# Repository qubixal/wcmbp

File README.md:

# Water Cooled MacBookPro (WCMBP)
> _this is part of a submission to Blueprint Hack Club._

**Hello!** I'm aiming to DIY the First True* Liquid Cooled Macbook utilising a sub-2.5mm Liquid Cooling Block, as well as creating the first Active Same-Level Hybrid Air-Liquid Cooling System In Consumer Electronics.
The first part of this readme will be a short introduction before this project is explained in more depth.

_render of the stock cooler of the Macbook Pro A2442._

## Function / Use
Similar to a traditional Desktop PC AIO, it features a pump, two fans (one blower one exhaust) and a modified refrigerator heatsink for a small size. 
<br>To use this project, simply plug in the quick disconnect tubing and plug the usbc line into a Macbook that has been prefitted with the heatsink and watch temps drop. 

## Why did I start this project?
I've always wanted to start making something but never found the determination to. 
My first attempt happened last year with me challenging myself to build the smallest drone i could, though those plans were cut short by my lack of experience and shipping problems (negotiating 4 months for the pcb) that destroyed my motivation. 
I wanted to push for a pioneer and revolutionary idea that improves technology, and had an idea at the end of last year to create the world's first true liquid cooled Macbook. 

I hope to make a high quality video out of this project too!
<br> **Thank you for reviewing this project.**

note: this repository is placed under CC BY-NC-ND.

## Hardware (Cooler)
The concept is simple, just pull water over the processor ...

The first design used parallel channels running from a supply manifold to a drain manifold, shortening single channels to reduce pressure drop.

To assist with water flow better, the second design smoothed out corners of the first.

## PCB
This project is powered using the STM32G431CBT6, as my friend also happen to be building a project of his using this chip.
The schematics are as follows.

There are a few errors in the schematic design, such as flashing components being forgotten T_T but I'm trying to find a workaround without buying another board.
The wiring is relatively straightforward, all the power supply is at the bottom and the main chip components to the centre, while peripherals are connected to the left.

I have finished soldering the board (only rich people can afford stencil T-T) and debugging USB data issues.

## Case
Original case

Somehow, not a **single** dimension fit. A round of revision and rebuilding the entire project again, ver2 is born.

The whole thing can be 3D printed in a few pieces.

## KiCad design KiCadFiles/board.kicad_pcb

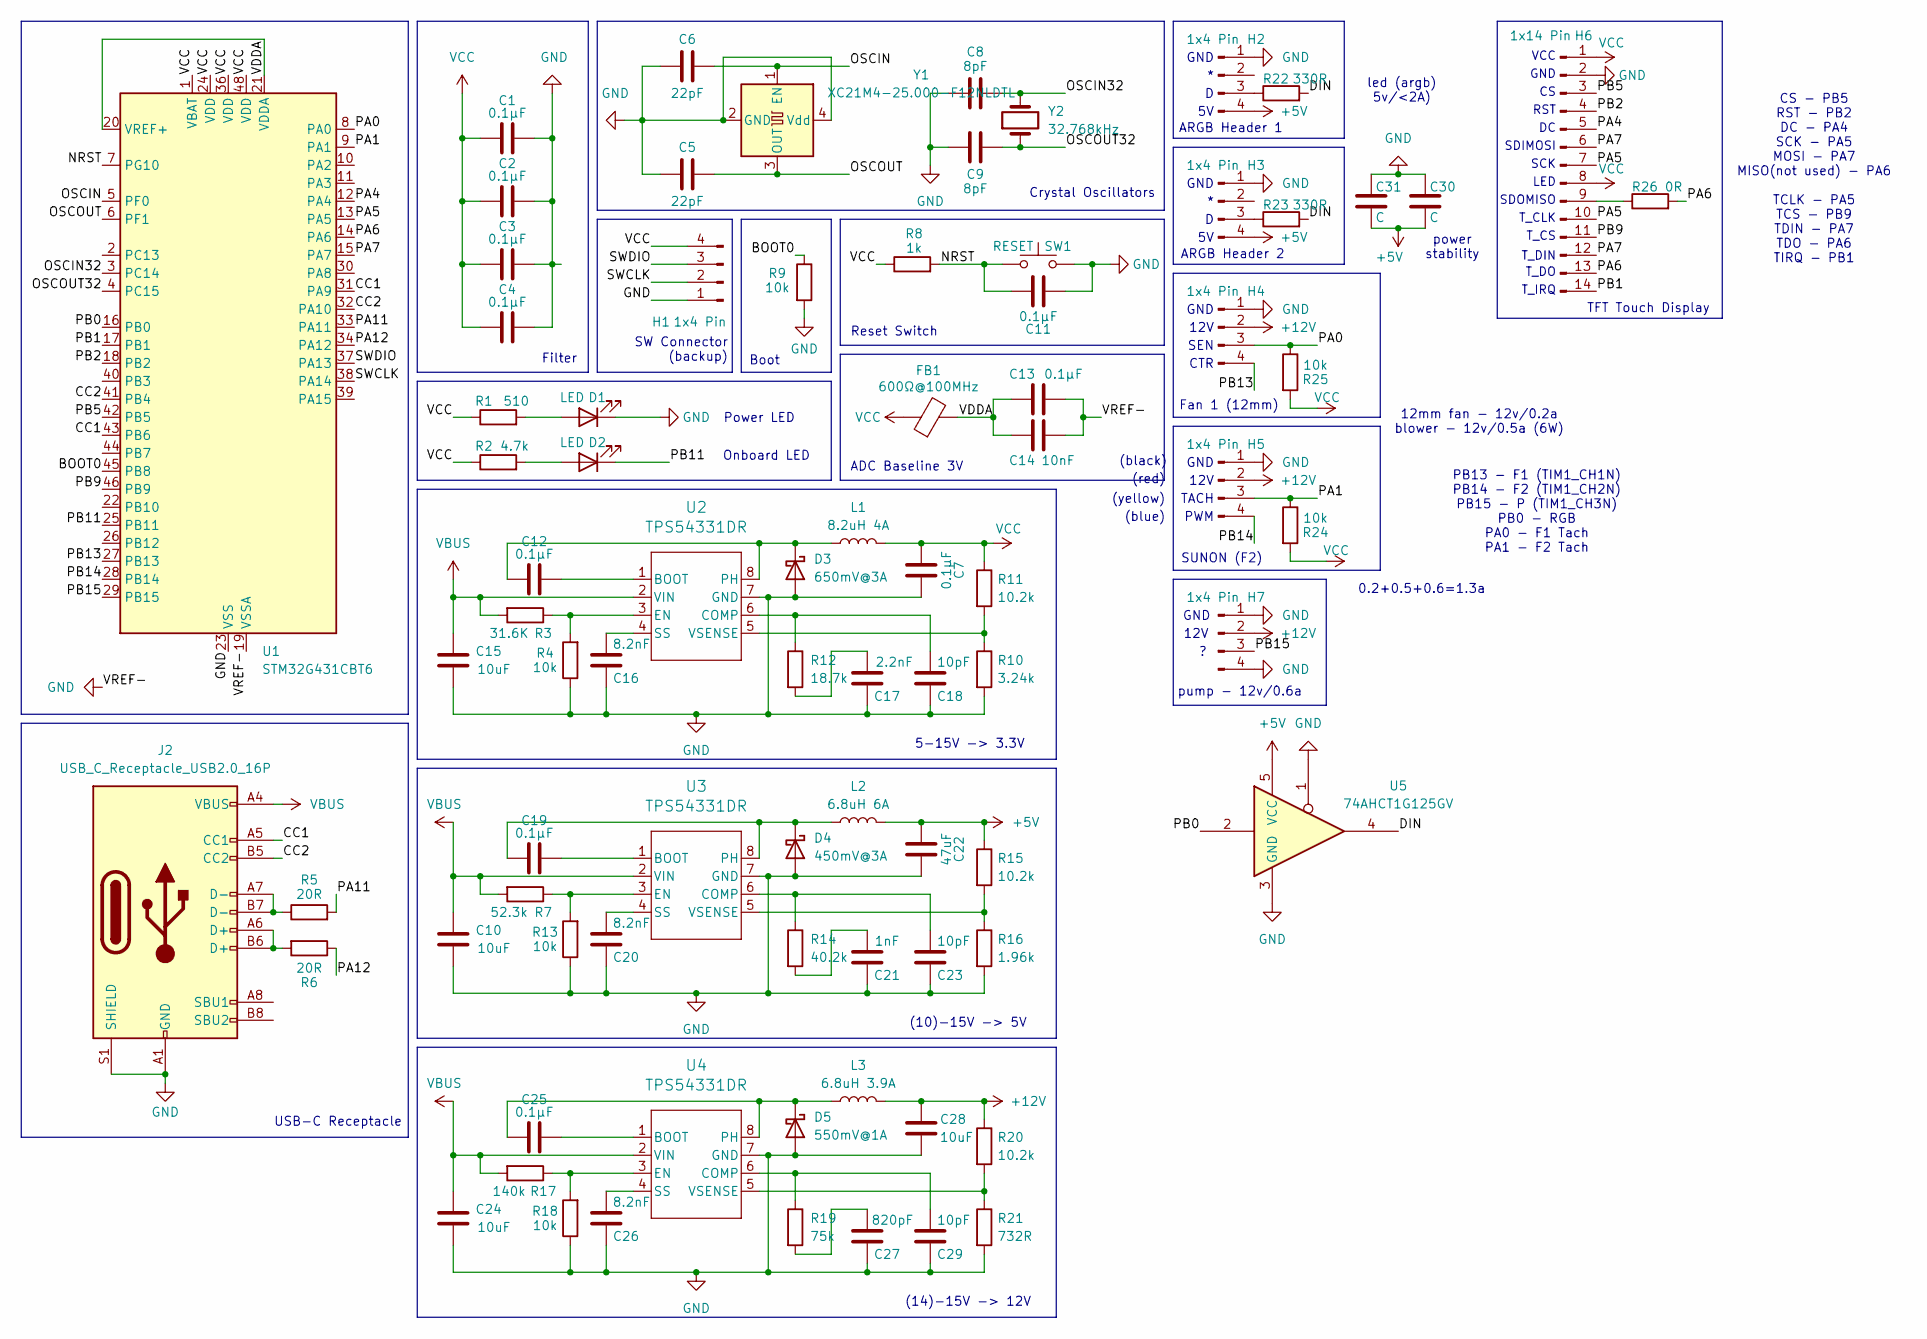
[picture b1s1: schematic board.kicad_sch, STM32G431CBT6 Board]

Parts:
C1, C2, C3, C4, C7, C11, C12, C13, C19, C25: 0.1μF; C_0805_2012Metric
C5, C6: 22pF; C_0805_2012Metric
C8, C9: 8pF; C_0805_2012Metric
C10, C15, C24, C28: 10uF; C_0805_2012Metric
C14: 10nF; C_0805_2012Metric
C16, C20, C26: 8.2nF; C_0805_2012Metric
C17: 2.2nF; C_0805_2012Metric
C18, C23, C29: 10pF; C_0805_2012Metric
C21: 1nF; C_0805_2012Metric
C22: 47uF; C_0805_2012Metric
C27: 820pF; C_0805_2012Metric
C30, C31: C; CP_Radial_D4.0mm_P2.00mm
D1, D2: LED; LED_0805_2012Metric
D3: 650mV@3A; D_1206_3216Metric
D4: 450mV@3A; D_SMA
D5: 550mV@1A; D_1812_4532Metric
FB1: 600Ω@100MHz; C_0805_2012Metric
H1, H2, H3, H4, H7: 1x4 Pin; PinHeader_1x04_P2.54mm_Vertical
H5: 1x4 Pin; PinSocket_1x04_P1.27mm_Vertical
H6: 1x14 Pin; PinHeader_1x14_P2.54mm_Vertical
J2: USB_C_Receptacle_USB2.0_16P; USB_C_Receptacle_GCT_USB4105-xx-A_16P_TopMnt_Horizontal
L1: 8.2uH 4A; BOURNS_SRN8040
L2: 6.8uH 6A; L_Taiyo-Yuden_MD-5050
L3: 6.8uH 3.9A; L_Changjiang_FTC404030S
R1: 510; R_0805_2012Metric
R2: 4.7k; R_0805_2012Metric
R3: 31.6K; R_0805_2012Metric
R4, R9, R13, R18, R24, R25: 10k; R_0805_2012Metric
R5, R6: 20R; R_0805_2012Metric
R7: 52.3k; R_0805_2012Metric
R8: 1k; R_0805_2012Metric
R10: 3.24k; R_0805_2012Metric
R11, R15, R20: 10.2k; R_0805_2012Metric
R12: 18.7k; R_0805_2012Metric
R14: 40.2k; R_0805_2012Metric
R16: 1.96k; R_0805_2012Metric
R17: 140k; R_0805_2012Metric
R19: 75k; R_0805_2012Metric
R21: 732R; R_0805_2012Metric
R22, R23: 330R; R_0805_2012Metric
R26: 0R; R_0201_0603Metric_Pad0.64x0.40mm_HandSolder
SW1: RESET; SW_SPST_TS-1088-xR020
U1: STM32G431CBT6; LQFP-48_7x7mm_P0.5mm
U2, U3, U4: TPS54331DR; TPS54331
U5: 74AHCT1G125GV; SOT-23-5
Y1: XC21M4-25.000-F12NLDTL; Crystal_SMD_2016-4Pin_2.0x1.6mm
Y2: 32.768kHz; Crystal_SMD_3215-2Pin_3.2x1.5mm

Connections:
+5V: C22.1, C30.2, C31.2, H2.4 (5V), H3.4 (5V), L2.2, R15.1, U5.5 (VCC)
+12V: C28.2, H4.2 (*), H5.2 (*), H7.2 (*), L3.2, R20.1
/BOOT0: R9.1, U1.45 (PB8)
/CC1: J2.A5 (CC1), U1.31 (PA9), U1.43 (PB6)
/CC2: J2.B5 (CC2), U1.32 (PA10), U1.41 (PB4)
/DIN: R22.2, R23.2, U5.4
/NRST: C11.2, R8.2, SW1.1, U1.7 (PG10)
/OSCIN: C6.2, U1.5 (PF0), Y1.1 (EN)
/OSCIN32: C8.2, U1.3 (PC14), Y2.2
/OSCOUT: C5.2, U1.6 (PF1), Y1.3 (OUT)
/OSCOUT32: C9.2, U1.4 (PC15), Y2.1
/PA0: H4.3 (D), R25.1, U1.8 (PA0)
/PA1: H5.3 (D), R24.1, U1.9 (PA1)
/PA4: H6.5, U1.12 (PA4)
/PA5: H6.7, H6.10, U1.13 (PA5)
/PA6: H6.13, R26.2, U1.14 (PA6)
/PA7: H6.6, H6.12, U1.15 (PA7)
/PA11: R5.2, U1.33 (PA11)
/PA12: R6.1, U1.34 (PA12)
/PB0: U1.16 (PB0), U5.2
/PB1: H6.14, U1.17 (PB1)
/PB2: H6.4, U1.18 (PB2)
/PB5: H6.3, U1.42 (PB5)
/PB9: H6.11, U1.46 (PB9)
/PB11: D2.1 (K), U1.25 (PB11)
/PB13: H4.4 (5V), U1.27 (PB13)
/PB14: H5.4 (5V), U1.28 (PB14)
/PB15: H7.3 (D), U1.29 (PB15)
/SWCLK: H1.2, U1.38 (PA14)
/SWDIO: H1.3, U1.37 (PA13)
/VDDA: C13.1, C14.2, FB1.2, U1.20 (VREF+), U1.21 (VDDA)
GND: C1.2, C2.2, C3.2, C4.2, C5.1, C6.1, C7.2, C8.1, C9.1, C10.1, C11.1, C13.2, C14.1, C15.1, C16.2, C17.2, C18.2, C20.2, C21.2, C22.2, C23.2, C24.1, C26.2, C27.2, C28.1, C29.2, C30.1, C31.1, D1.1 (K), D3.2 (A), D4.2 (A), D5.2 (A), H1.1, H2.1 (GND), H3.1 (GND), H4.1 (GND), H5.1 (GND), H6.2, H7.1 (GND), H7.4 (5V), J2.A1 (GND), J2.A12 (GND), J2.B1 (GND), J2.B12 (GND), J2.S1 (SHIELD), R4.1, R9.2, R10.2, R13.1, R16.2, R18.1, R21.2, SW1.2, U1.19 (VSSA), U1.23 (VSS), U1.35 (VSS), U1.47 (VSS), U2.7 (GND), U3.7 (GND), U4.7 (GND), U5.1, U5.3 (GND), Y1.2 (GND), Y1.4 (Vdd)
unnamed: C17.1, R12.2
unnamed: C21.1, R14.2
unnamed: C27.1, R19.2
unnamed: D1.2 (A), R1.2
unnamed: D2.2 (A), R2.2
unnamed: C12.1, D3.1 (K), L1.1, U2.8 (PH)
unnamed: C19.1, D4.1 (K), L2.1, U3.8 (PH)
unnamed: C25.1, D5.1 (K), L3.1, U4.8 (PH)
unnamed: H2.3 (D), R22.1
unnamed: H3.3 (D), R23.1
unnamed: H6.9, R26.1
unnamed: J2.A6 (D+), J2.B6 (D+), R6.2
unnamed: J2.A7 (D-), J2.B7 (D-), R5.1
unnamed: C12.2, U2.1 (BOOT)
unnamed: C18.1, R12.1, U2.6 (COMP)
unnamed: R3.1, R4.2, U2.3 (EN)
unnamed: C16.1, U2.4 (SS)
unnamed: R10.1, R11.2, U2.5 (VSENSE)
unnamed: C19.2, U3.1 (BOOT)
unnamed: C23.1, R14.1, U3.6 (COMP)
unnamed: R7.1, R13.2, U3.3 (EN)
unnamed: C20.1, U3.4 (SS)
unnamed: R15.2, R16.1, U3.5 (VSENSE)
unnamed: C25.2, U4.1 (BOOT)
unnamed: C29.1, R19.1, U4.6 (COMP)
unnamed: R17.1, R18.2, U4.3 (EN)
unnamed: C26.1, U4.4 (SS)
unnamed: R20.2, R21.1, U4.5 (VSENSE)
VBUS: C10.2, C15.2, C24.2, J2.A4 (VBUS), J2.A9 (VBUS), J2.B4 (VBUS), J2.B9 (VBUS), R3.2, R7.2, R17.2, U2.2 (VIN), U3.2 (VIN), U4.2 (VIN)
VCC: C1.1, C2.1, C3.1, C4.1, C7.1, FB1.1, H1.4, H6.1, H6.8, L1.2, R1.1, R2.1, R8.1, R11.1, R24.2, R25.2, U1.1 (VBAT), U1.24 (VDD), U1.36 (VDD), U1.48 (VDD)

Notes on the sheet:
Reset Switch
SDIMOSI
(yellow)
CS - PB5 RST - PB2 DC - PA4 SCK - PA5 MOSI - PA7 MISO(not used) - PA6 TCLK - PA5 TCS - PB9 TDIN - PA7 TDO - PA6 TIRQ - PB1
GND
Fan 1 (12mm)
0.2+0.5+0.6=1.3a
USB-C Receptacle
RST
SUNON (F2)
Power LED
ARGB Header 1
12V
(14)-15V -> 12V
5-15V -> 3.3V
ARGB Header 2
SDOMISO
TACH
12mm fan - 12v/0.2a blower - 12v/0.5a (6W)
(10)-15V -> 5V
ADC Baseline 3V
Boot
(black)
SCK
Filter
(blue)
T_DIN
(red)
CTR
T_CS
T_CLK
VCC
PWM
Onboard LED
T_DO
pump - 12v/0.6a
SW Connector (backup)
LED
TFT Touch Display
T_IRQ

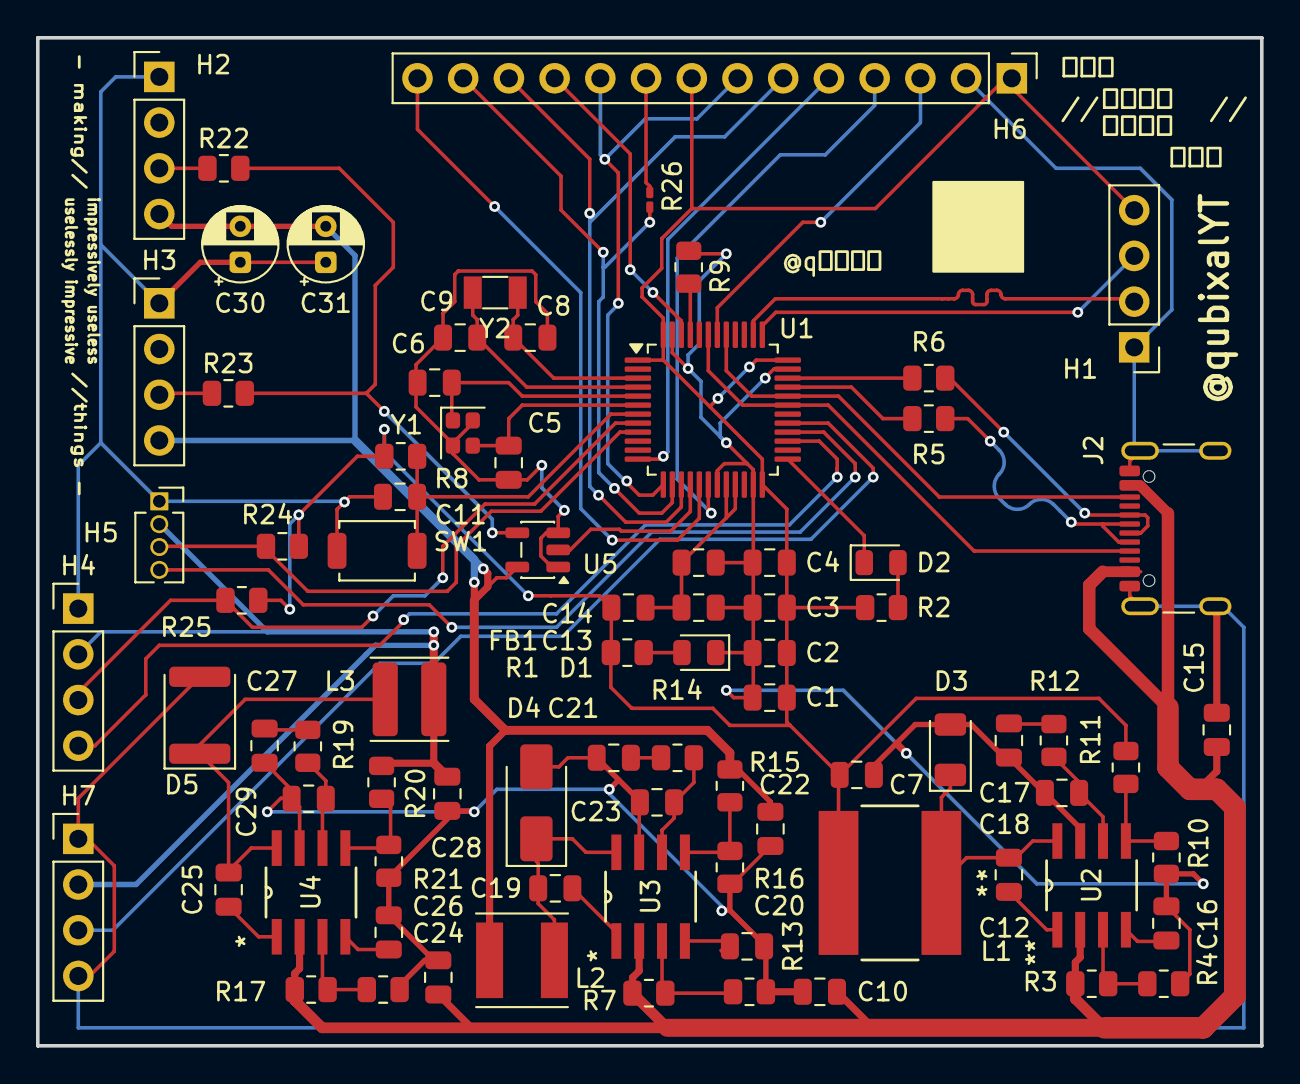
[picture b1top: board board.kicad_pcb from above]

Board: 2 copper layers, 68.0 x 56.0 mm, 82 parts (0 on the bottom side), 62 nets.

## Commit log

2026-03-07 readme update
    commit
2026-03-07 Add files via upload
    pcb/bom parts files
2026-03-07 kicad files
2026-03-07 license
2026-03-07 Include CC BY-NC-ND license note in README
    Added a note about the repository's license.
2026-03-12 case 3d file
2026-03-12 non pcb bom
2026-03-31 Create a
2026-03-31 Rename assembled.png to images/assembled.png
2026-03-31 Rename disassembled.png to images/disassembled.png
2026-03-31 Rename image_2026-03-31_222305330.png to images/pcbschematics
2026-03-31 Rename image_2026-03-31_222312539.png to images/pcbwiring
2026-03-31 Rename image_2026-03-31_222321727.png to images/stockcooler
2026-03-31 Rename image_2026-03-31_222331664.png to images/conceptidea
2026-03-31 Rename image_2026-03-31_222336672.png to idea1
2026-03-31 Rename idea1 to images/coolerv1
2026-03-31 Rename ver1.png to images/ver1.png
2026-03-31 Rename image_2026-03-31_222342295.png to images/coolerv2
2026-03-31 Rename coolerv2 to coolerv2.png
2026-03-31 Rename coolerv1 to coolerv1.png
2026-03-31 Rename pcbschematics to pcbschematics.png
2026-03-31 Rename pcbwiring to pcbwiring.png
2026-03-31 Rename stockcooler to stockcooler.png
2026-03-31 Rename conceptidea to conceptidea.png
2026-03-31 Rename image_2026-03-31_225726215.png to pcb.png
2026-03-31 Rename wiring.png to pcbwiring.png
